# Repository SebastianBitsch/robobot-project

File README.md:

### Getting started

1. Connect to robot 
  ```bash
  ssh local@10.197.216.74
  ```

2. Login
  ```password: grenen```

3. Build
  ```bash
  cd svn/robobot/raubase/build && make
  ```

4. Run
  ```bash
  cd svn/robobot/raubase/build && ./raubase
  ```

### Tips and tricks
- Moving files from ```ssh``` to ```local```. On a terminal on your local machine: 
  ```bash
  scp -r local@10.197.216.74:/home/local/svn<PATH_TO_FILE> <LOCAL_PATH>
  ```
  - For instance:
  ```bash
  scp -r local@10.197.216.74:/home/local/svn/robobot/raubase/build/img/ /Users/sebastianbitsch/Desktop/
  ```

# Camera
Access the stream
```bash
cd svn/robobot/raubase/build/
motion
```
See the output stream at <http://10.197.216.74:8081>

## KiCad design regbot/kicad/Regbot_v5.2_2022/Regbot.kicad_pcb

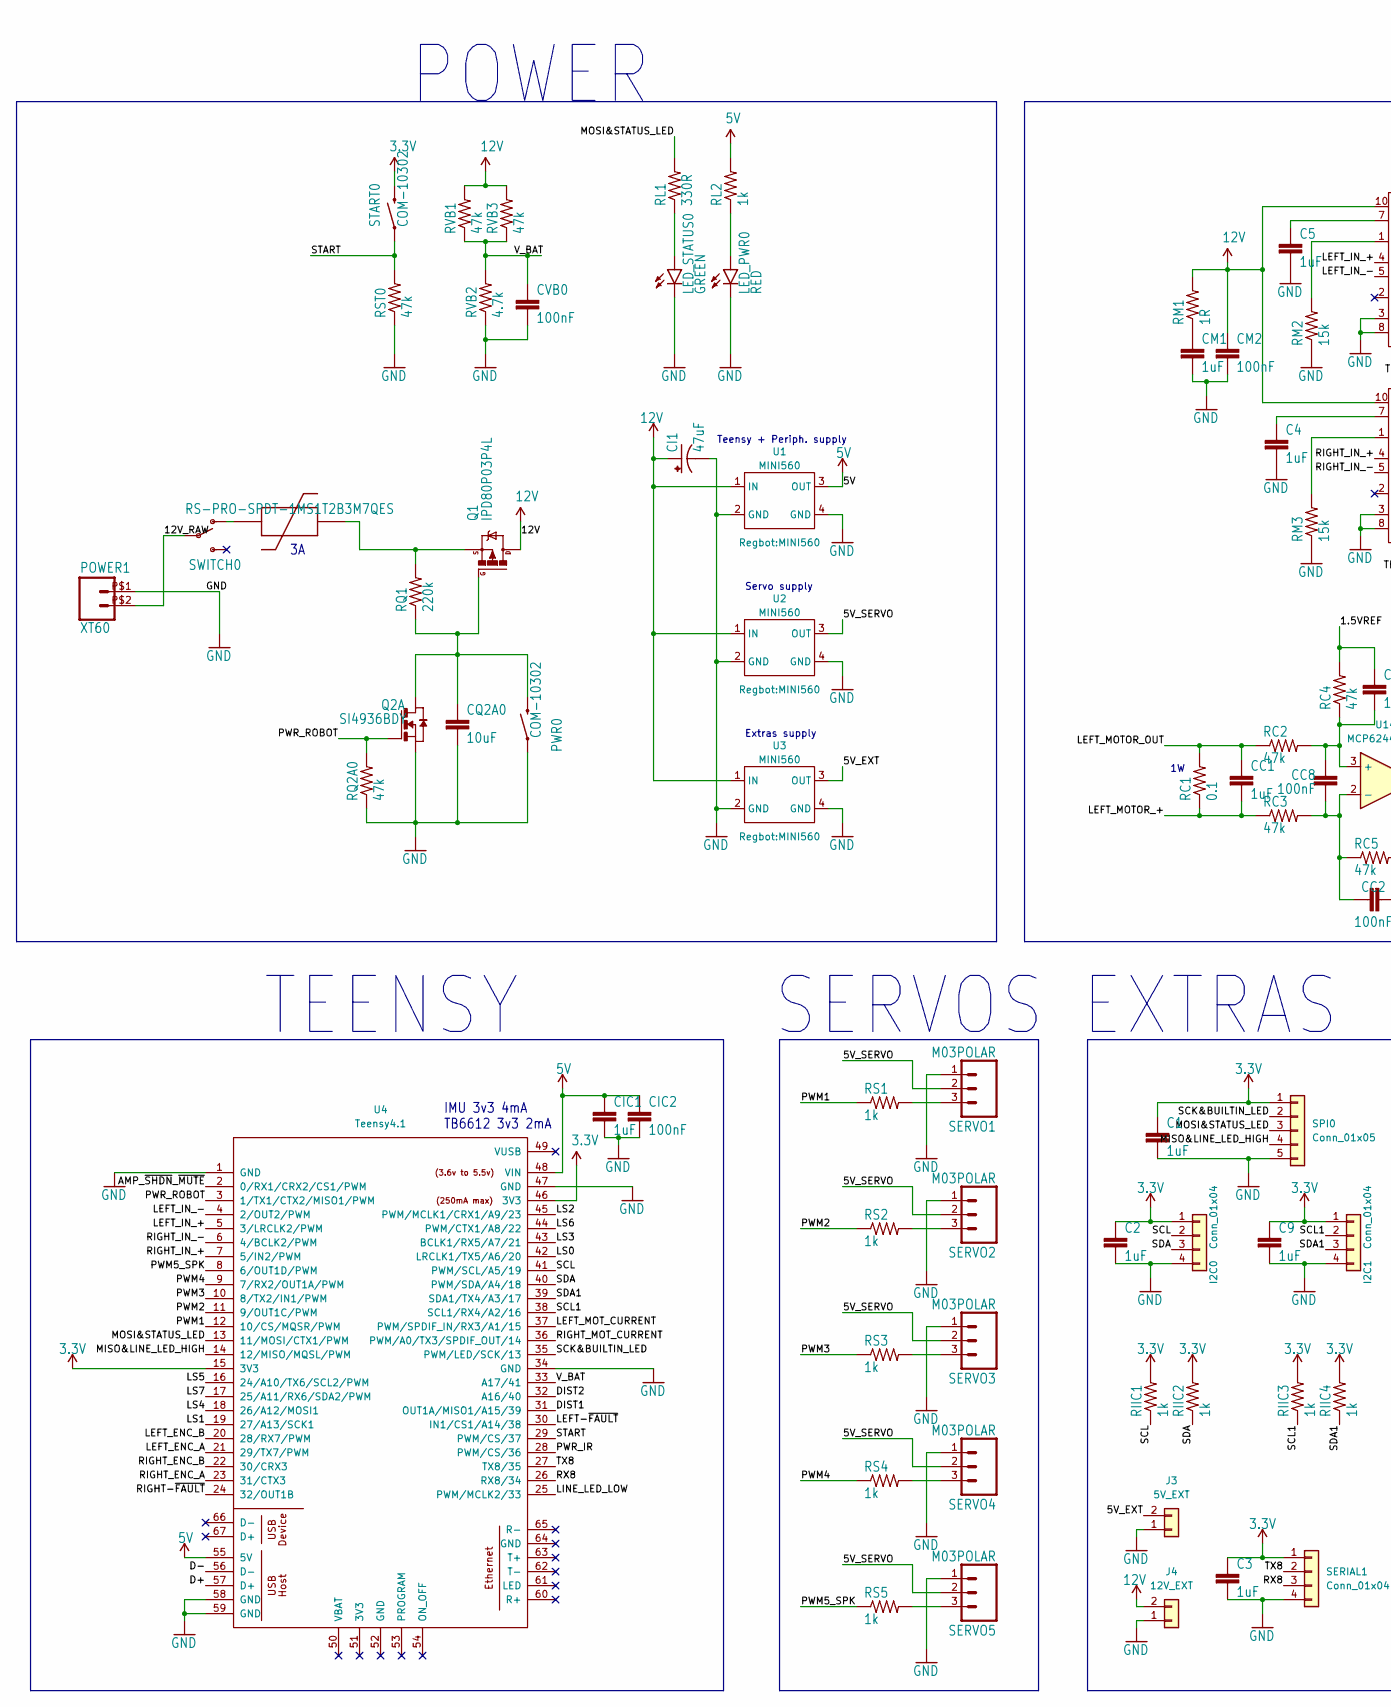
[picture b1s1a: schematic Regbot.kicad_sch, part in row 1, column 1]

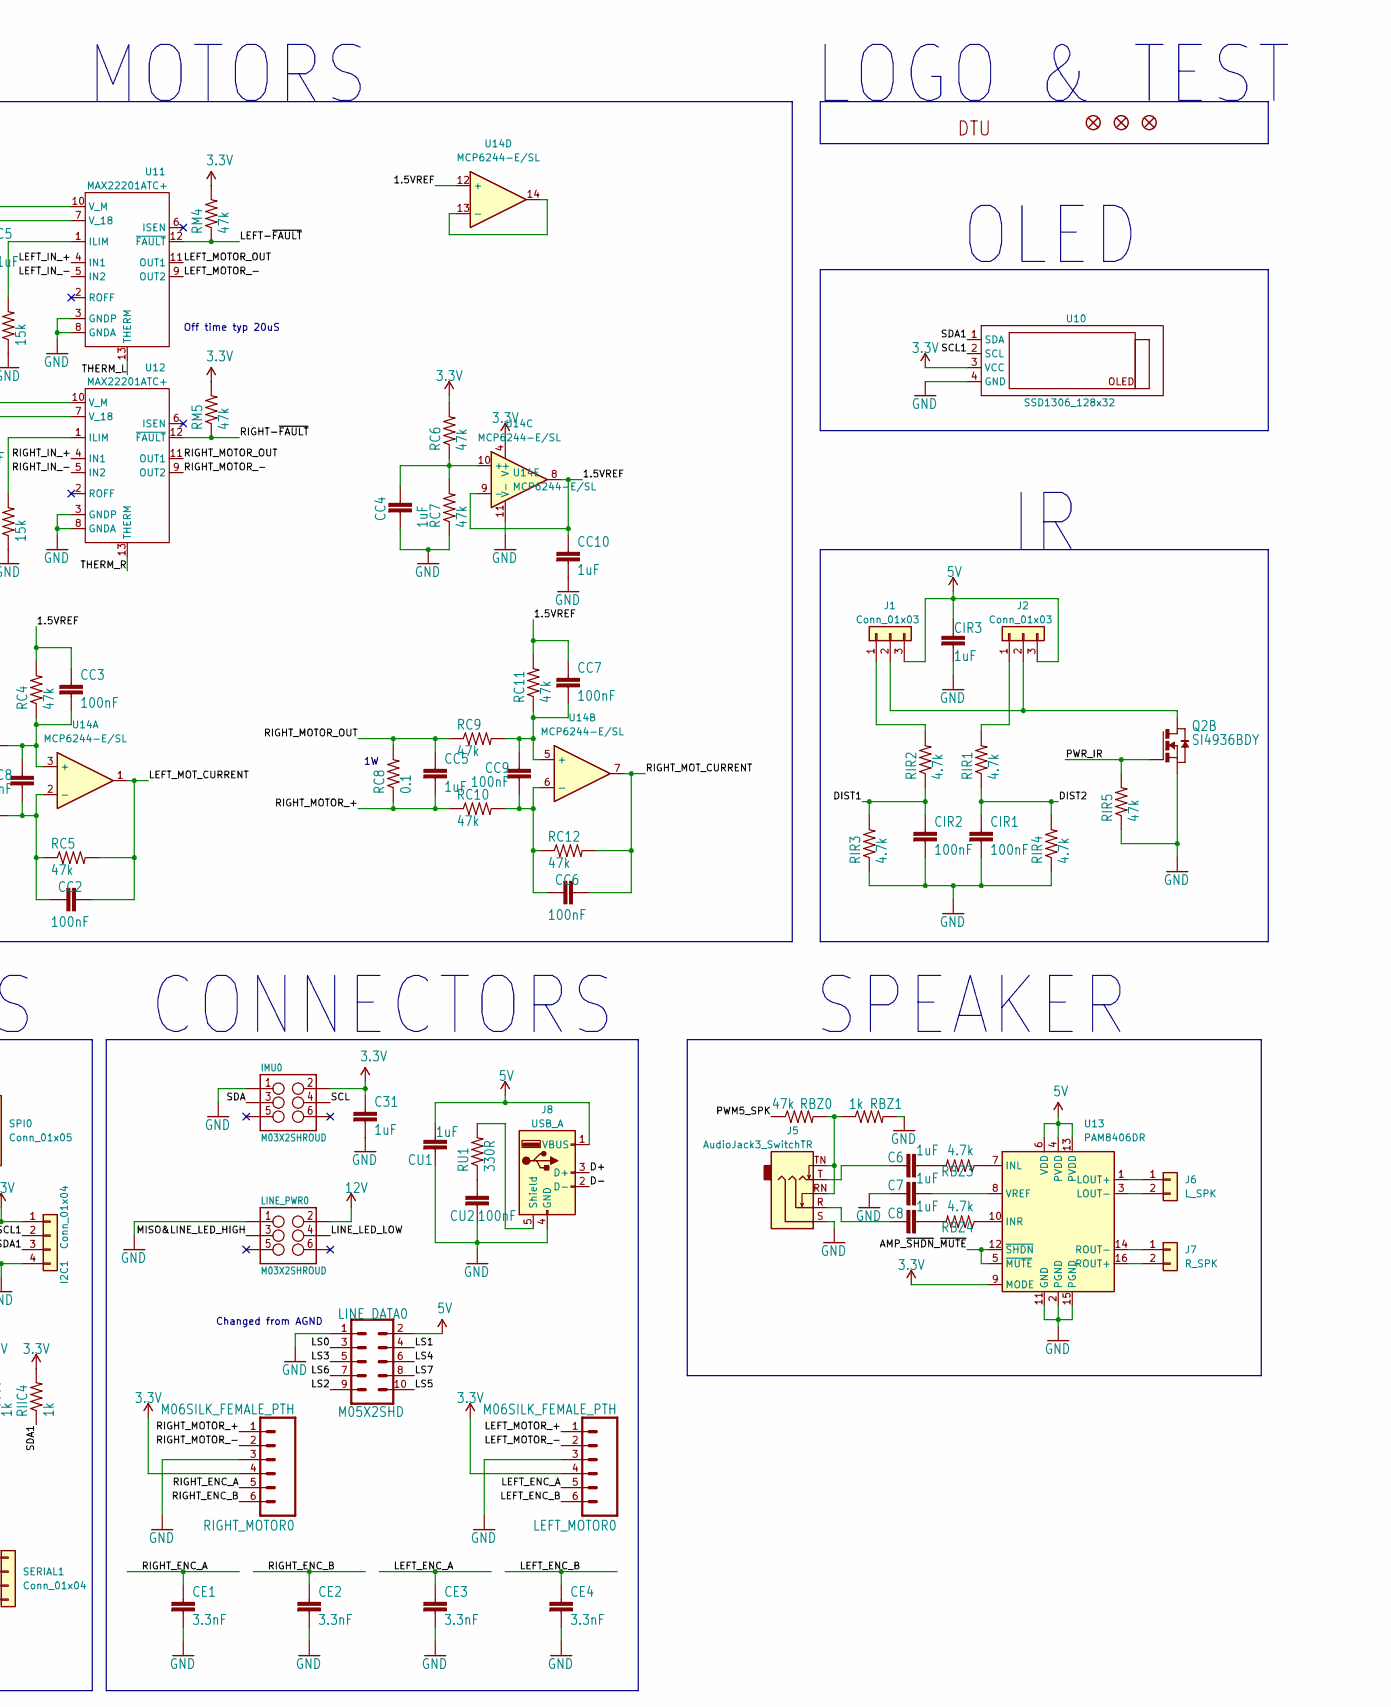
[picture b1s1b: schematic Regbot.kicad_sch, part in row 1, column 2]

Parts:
C1, C2, C3, C4, C5, C6, C7, C8, C9, C31: 1uF; 0805
CC1, CC4, CC5, CC10: 1uF; 0805
CC2, CC3, CC6, CC7, CC8, CC9: 100nF; 0805
CE1, CE2, CE3, CE4: 3.3nF; 0805
CI1: 47uF; PANASONIC_D_XL
CIC1: 1uF; 0805
CIC2: 100nF; 0805
CIR1, CIR2: 100nF; 0805
CIR3: 1uF; 0805
CM1: 1uF; 0805
CM2: 100nF; 0805
CQ2A0: 10uF; 1210
CU1: 1uF; 0805
CU2: 100nF; 0805
CVB0: 100nF; 0805
FD1, FD2, FD3: FIDUCIAL1X2; FIDUCIAL-1X2
I2C0, I2C1: Conn_01x04; JST_PH_B4B-PH-K_1x04_P2.00mm_Vertical
IMU0: 2X3-SHROUDED
J1, J2: Conn_01x03; JST_PH_B3B-PH-K_1x03_P2.00mm_Vertical
J3: 5V_EXT; JST_PH_B2B-PH-K_1x02_P2.00mm_Vertical
J4: 12V_EXT; JST_PH_B2B-PH-K_1x02_P2.00mm_Vertical
J5: AudioJack3_SwitchTR; STX-3680-5NB
J6: L_SPK; JST_PH_B2B-PH-K_1x02_P2.00mm_Vertical
J7: R_SPK; JST_PH_B2B-PH-K_1x02_P2.00mm_Vertical
J8: USB_A; USB_A_ASSMANN_A-TOP_VERTICAL
LED_PWR0: RED; LED-1206
LED_STATUS0: GREEN; LED-1206
LEFT_MOTOR0: M06SILK_FEMALE_PTH; 1X06
LINE_DATA0: 2X5-SHROUDED
LINE_PWR0: 2X3-SHROUDED
MAIN_FUSE0: SMF_OMNI-BLOK_FUSE_BLOCK
POWER1: XT60
PWR0: COM-10302; TACTILE-PTH-12MM
Q1: D-PAK_TO252AA
Q2: SI4936BDY; SO8
RBZ0: 47k; 0805
RBZ1: 1k; 0805
RBZ3, RBZ4: 4.7k; 0805
RC1, RC8: 0.1; R_1206_3216Metric
RC2, RC3, RC4, RC5, RC6, RC7, RC9, RC10, RC11, RC12: 47k; 0805
RIGHT_MOTOR0: M06SILK_FEMALE_PTH; 1X06
RIIC1, RIIC2, RIIC3, RIIC4: 1k; 0805
RIR1, RIR2, RIR3, RIR4: 4.7k; 0805
RIR5: 47k; 0805
RL1: 330R; 0805
RL2: 1k; 0805
RM1: 1R; 0805
RM2, RM3: 15k; 0805
RM4, RM5: 47k; 0805
RQ1: 220k; 0805
RQ2A0: 47k; 0805
RS1, RS2, RS3, RS4, RS5: 1k; 0805
RST0: 47k; 0805
RU1: 330R; 0805
RVB1, RVB3: 47k; 0805
RVB2: 4.7k; 0805
SERIAL1: Conn_01x04; JST_PH_B4B-PH-K_1x04_P2.00mm_Vertical
SERVO1, SERVO2, SERVO3, SERVO4, SERVO5: M03POLAR; MOLEX-1X3
SPI0: Conn_01x05; JST_PH_B5B-PH-K_1x05_P2.00mm_Vertical
START0: COM-10302; TACTILE-PTH-12MM
SWITCH0: RS-PRO-1MS1T2B3M7QES
U1, U2, U3: MINI560
U4: Teensy4.1; Teensy41
U10: SSD1306_128x32
U11, U12: MAX22201ATC+; SON50P300X300X80-13N
U13: PAM8406DR; SOP-16_3.9x9.9mm_P1.27mm
U14: MCP6244-E/SL; SOIC-14_3.9x8.7mm_P1.27mm
U$1: DTUMEDIUM-9MM; DTU-MEDIUM-9MM

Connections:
3.3V: C1.1, C2.1, C3.1, C9.1, C31.1, I2C0.1, I2C1.1, IMU0.2, LEFT_MOTOR0.4, RC6.2, RIGHT_MOTOR0.4, RIIC1.2, RIIC2.2, RIIC3.2, RIIC4.2, RM4.2, RM5.2, SERIAL1.1, SPI0.1, START0.3, START0.4, U4.15 (3V3), U4.46 (3V3), U10.3 (VCC), U13.9 (MODE), U14.4 (V+)
5V: CIC1.1, CIC2.1, CIR3.1, CU1.1, J1.3, J2.3, J8.1 (VBUS), LINE_DATA0.2, RL2.2, U1.3 (OUT), U4.48 (VIN), U4.55 (5V), U13.4 (PVDD), U13.6 (VDD), U13.13 (PVDD)
12V: CI1.+, CM2.1, J4.2, LINE_PWR0.2, Q1.4 (D), RM1.2, RVB1.2, RVB3.2, U1.1 (IN), U2.1 (IN), U3.1 (IN), U11.10 (V_M), U12.10 (V_M)
/1.5VREF: CC3.1, CC7.1, CC10.1, RC4.2, RC11.2, U14.8, U14.9 (-), U14.12 (+)
/5V_EXT: J3.2, U3.3 (OUT)
/5V_SERVO: SERVO1.2, SERVO2.2, SERVO3.2, SERVO4.2, SERVO5.2, U2.3 (OUT)
/12V_RAW: POWER1.P$2 (2), SWITCH0.P$2 (P2)
/AMP_~SHDN_~MUTE: U4.2 (0/RX1/CRX2/CS1/PWM), U13.5 (~MUTE), U13.12 (~SHDN)
/D+: J8.3 (D+), U4.57 (D+)
/D-: J8.2 (D-), U4.56 (D-)
/DIST1: CIR2.1, RIR2.1, RIR3.2, U4.31 (OUT1A/MISO1/A15/39)
/DIST2: CIR1.1, RIR1.1, RIR4.2, U4.32 (A16/40)
/LEFT-~FAULT: RM4.1, U4.30 (IN1/CS1/A14/38), U11.12 (~FAULT)
/LEFT_ENC_A: CE3.1, LEFT_MOTOR0.5, U4.21 (29/TX7/PWM)
/LEFT_ENC_B: CE4.1, LEFT_MOTOR0.6, U4.20 (28/RX7/PWM)
/LEFT_IN_+: U4.5 (3/LRCLK2/PWM), U11.4 (IN1)
/LEFT_IN_-: U4.4 (2/OUT2/PWM), U11.5 (IN2)
/LEFT_MOTOR_+: CC1.2, LEFT_MOTOR0.1, RC1.1, RC3.1
/LEFT_MOTOR_-: LEFT_MOTOR0.2, U11.9 (OUT2)
/LEFT_MOTOR_OUT: CC1.1, RC1.2, RC2.1, U11.11 (OUT1)
/LEFT_MOT_CURRENT: CC2.1, RC5.2, U4.37 (PWM/SPDIF_IN/RX3/A1/15), U14.1
/LINE_LED_LOW: LINE_PWR0.4, U4.25 (PWM/MCLK2/33)
/LS0: LINE_DATA0.3, U4.42 (LRCLK1/TX5/A6/20)
/LS1: LINE_DATA0.4, U4.19 (27/A13/SCK1)
/LS2: LINE_DATA0.9, U4.45 (PWM/MCLK1/CRX1/A9/23)
/LS3: LINE_DATA0.5, U4.43 (BCLK1/RX5/A7/21)
/LS4: LINE_DATA0.6, U4.18 (26/A12/MOSI1)
/LS5: LINE_DATA0.10, U4.16 (24/A10/TX6/SCL2/PWM)
/LS6: LINE_DATA0.7, U4.44 (PWM/CTX1/A8/22)
/LS7: LINE_DATA0.8, U4.17 (25/A11/RX6/SDA2/PWM)
/MISO&LINE_LED_HIGH: LINE_PWR0.3, SPI0.4, U4.14 (12/MISO/MQSL/PWM)
/MOSI&STATUS_LED: RL1.2, SPI0.3, U4.13 (11/MOSI/CTX1/PWM)
/PWM1: RS1.1, U4.12 (10/CS/MQSR/PWM)
/PWM2: RS2.1, U4.11 (9/OUT1C/PWM)
/PWM3: RS3.1, U4.10 (8/TX2/IN1/PWM)
/PWM4: RS4.1, U4.9 (7/RX2/OUT1A/PWM)
/PWM5_SPK: RBZ0.1, RS5.1, U4.8 (6/OUT1D/PWM)
/PWR_IR: Q2.4 (G), RIR5.2, U4.28 (PWM/CS/36)
/PWR_ROBOT: Q2.2 (G), RQ2A0.2, U4.3 (1/TX1/CTX2/MISO1/PWM)
/RIGHT-~FAULT: RM5.1, U4.24 (32/OUT1B), U12.12 (~FAULT)
/RIGHT_ENC_A: CE1.1, RIGHT_MOTOR0.5, U4.23 (31/CTX3)
/RIGHT_ENC_B: CE2.1, RIGHT_MOTOR0.6, U4.22 (30/CRX3)
/RIGHT_IN_+: U4.7 (5/IN2/PWM), U12.4 (IN1)
/RIGHT_IN_-: U4.6 (4/BCLK2/PWM), U12.5 (IN2)
/RIGHT_MOTOR_+: CC5.2, RC8.1, RC10.1, RIGHT_MOTOR0.1
/RIGHT_MOTOR_-: RIGHT_MOTOR0.2, U12.9 (OUT2)
/RIGHT_MOTOR_OUT: CC5.1, RC8.2, RC9.1, U12.11 (OUT1)
/RIGHT_MOT_CURRENT: CC6.1, RC12.2, U4.36 (PWM/A0/TX3/SPDIF_OUT/14), U14.7
/RX8: SERIAL1.3, U4.26 (RX8/34)
/SCK&BUILTIN_LED: SPI0.2, U4.35 (PWM/LED/SCK/13)
/SCL: I2C0.2, IMU0.4, RIIC1.1, U4.41 (PWM/SCL/A5/19)
/SCL1: I2C1.2, RIIC3.1, U4.38 (SCL1/RX4/A2/16), U10.2 (SCL)
/SDA: I2C0.3, IMU0.3, RIIC2.1, U4.40 (PWM/SDA/A4/18)
/SDA1: I2C1.3, RIIC4.1, U4.39 (SDA1/TX4/A3/17), U10.1 (SDA)
/START: RST0.2, START0.1, START0.2, U4.29 (PWM/CS/37)
/THERM_L: U11.13 (THERM)
/THERM_R: U12.13 (THERM)
/TX8: SERIAL1.2, U4.27 (TX8/35)
/V_BAT: CVB0.1, RVB1.1, RVB2.2, RVB3.1, U4.33 (A17/41)
GND: C1.2, C2.2, C3.2, C4.2, C5.2, C7.1, C9.2, C31.2, CC4.2, CC10.2, CE1.2, CE2.2, CE3.2, CE4.2, CI1.-, CIC1.2, CIC2.2, CIR1.2, CIR2.2, CIR3.2, CM1.2, CM2.2, CQ2A0.2, CU1.2, CU2.2, CVB0.2, I2C0.4, I2C1.4, IMU0.1, J3.1, J4.1, J5.S, J8.4 (GND), LED_PWR0.C, LED_STATUS0.C, LEFT_MOTOR0.3, LINE_DATA0.1, LINE_PWR0.1, POWER1.P$1 (1), PWR0.1, PWR0.2, Q2.1 (S), Q2.3 (S), RBZ1.2, RC7.1, RIGHT_MOTOR0.3, RIR3.1, RIR4.1, RIR5.1, RM2.1, RM3.1, RQ2A0.1, RST0.1, RVB2.1, SERIAL1.4, SERVO1.1, SERVO2.1, SERVO3.1, SERVO4.1, SERVO5.1, SPI0.5, U1.2 (GND), U1.4 (GND), U2.2 (GND), U2.4 (GND), U3.2 (GND), U3.4 (GND), U4.1 (GND), U4.34 (GND), U4.47 (GND), U4.58 (GND), U4.59 (GND), U10.4 (GND), U11.3 (GNDP), U11.8 (GNDA), U12.3 (GNDP), U12.8 (GNDA), U13.2 (PGND), U13.11 (GND), U13.15 (PGND), U14.11 (V-)
unnamed: C4.1, U12.7 (V_18)
unnamed: C5.1, U11.7 (V_18)
unnamed: C6.1, J5.T
unnamed: C6.2, RBZ3.2
unnamed: C7.2, U13.8 (VREF)
unnamed: C8.1, J5.R
unnamed: C8.2, RBZ4.2
unnamed: CC2.2, CC8.2, RC3.2, RC5.1, U14.2 (-)
unnamed: CC3.2, CC8.1, RC2.2, RC4.1, U14.3 (+)
unnamed: CC4.1, RC6.1, RC7.2, U14.10 (+)
unnamed: CC6.2, CC9.2, RC10.2, RC12.1, U14.6 (-)
unnamed: CC7.2, CC9.1, RC9.2, RC11.1, U14.5 (+)
unnamed: CM1.1, RM1.1
unnamed: CQ2A0.1, PWR0.3, PWR0.4, Q1.1 (G), Q2.7 (D), Q2.8 (D), RQ1.1
unnamed: CU2.1, RU1.1
unnamed: J1.1, RIR2.2
unnamed: J1.2, J2.2, Q2.5 (D), Q2.6 (D)
unnamed: J2.1, RIR1.2
unnamed: J5.RN, J5.TN, RBZ0.2, RBZ1.1
unnamed: J6.1, U13.1 (LOUT+)
unnamed: J6.2, U13.3 (LOUT-)
unnamed: J7.1, U13.14 (ROUT-)
unnamed: J7.2, U13.16 (ROUT+)
unnamed: J8.5 (Shield), RU1.2
unnamed: LED_PWR0.A, RL2.1
unnamed: LED_STATUS0.A, RL1.1
unnamed: MAIN_FUSE0.PIN1, Q1.3 (S), RQ1.2
unnamed: MAIN_FUSE0.PIN2, SWITCH0.P$1 (O1)
unnamed: RBZ3.1, U13.7 (INL)
unnamed: RBZ4.1, U13.10 (INR)
unnamed: RM2.2, U11.1 (ILIM)
unnamed: RM3.2, U12.1 (ILIM)
unnamed: RS1.2, SERVO1.3
unnamed: RS2.2, SERVO2.3
unnamed: RS3.2, SERVO3.3
unnamed: RS4.2, SERVO4.3
unnamed: RS5.2, SERVO5.3
unnamed: U14.13 (-), U14.14

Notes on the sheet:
Changed from AGND
IMU 3v3 4mA TB6612 3v3 2mA
SPEAKER
Off time typ 20uS
Teensy + Periph. supply
TEENSY
Servo supply
MOTORS
POWER
SERVOS
OLED
EXTRAS
LOGO & TEST
CONNECTORS
Extras supply

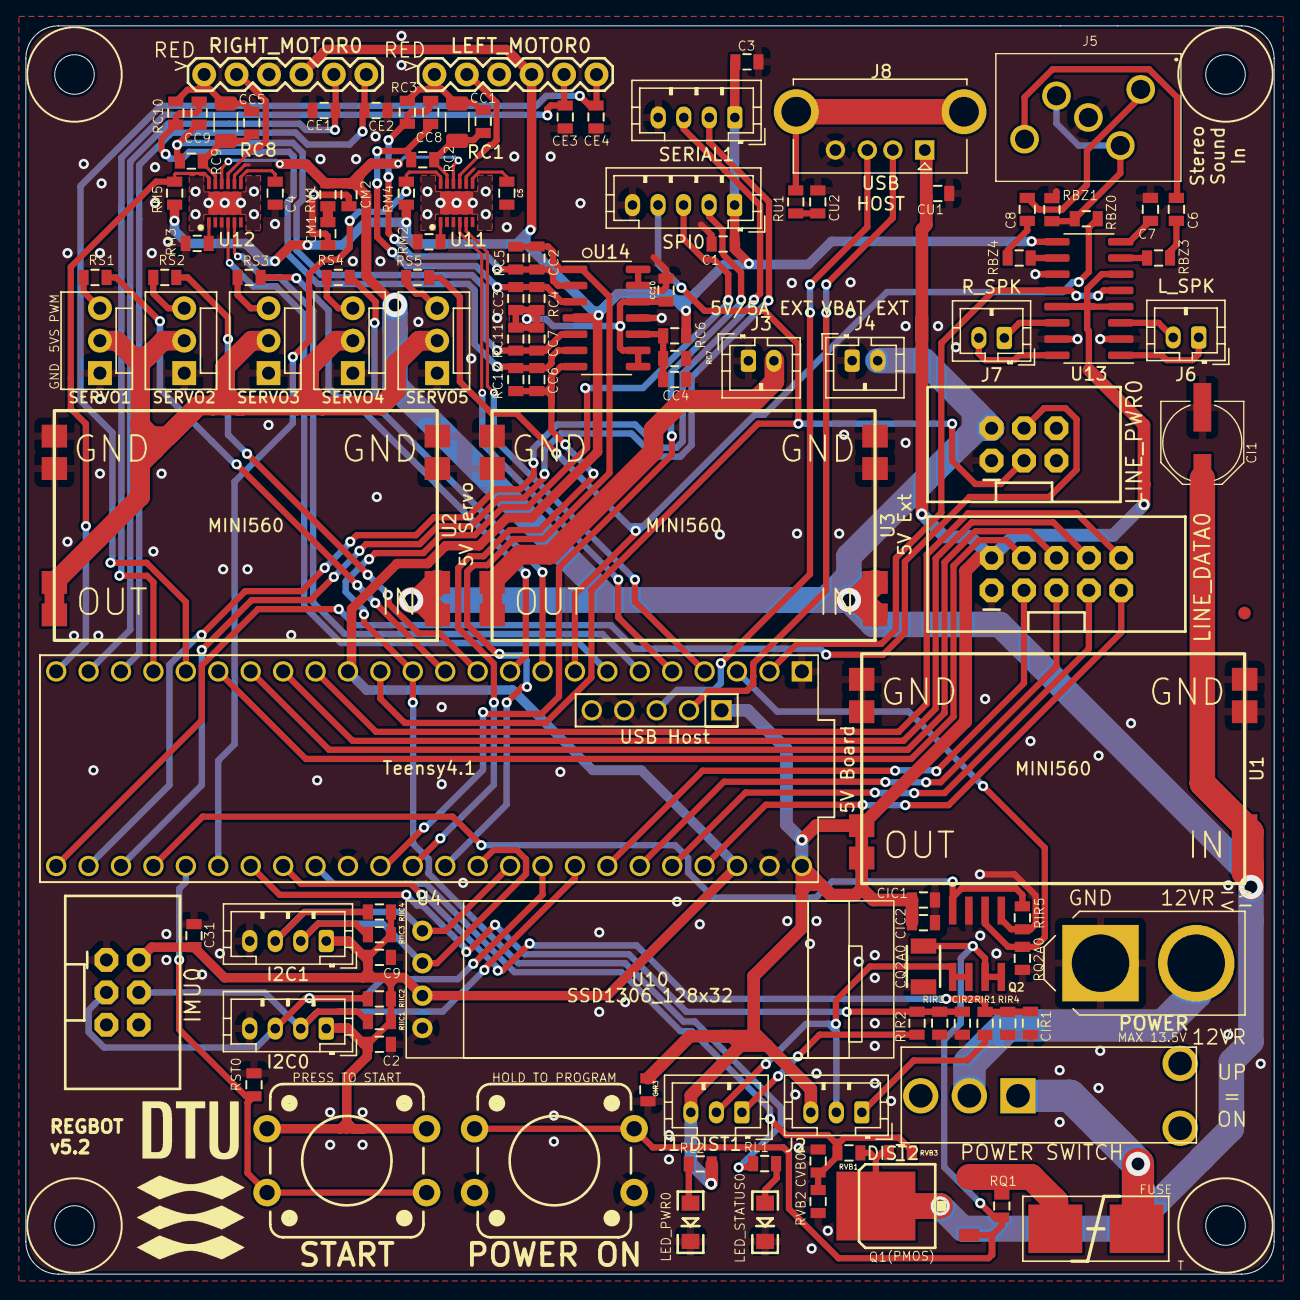
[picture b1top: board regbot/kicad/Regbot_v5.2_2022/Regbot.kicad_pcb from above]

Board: 2 copper layers, 97.8 x 97.8 mm, 129 parts (1 on the bottom side), 96 nets.

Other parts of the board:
@HOLE0, @HOLE1, @HOLE2, @HOLE3: (no value)
U$1#2: DTUMEDIUM-9MM; DTU-MEDIUM-9MM

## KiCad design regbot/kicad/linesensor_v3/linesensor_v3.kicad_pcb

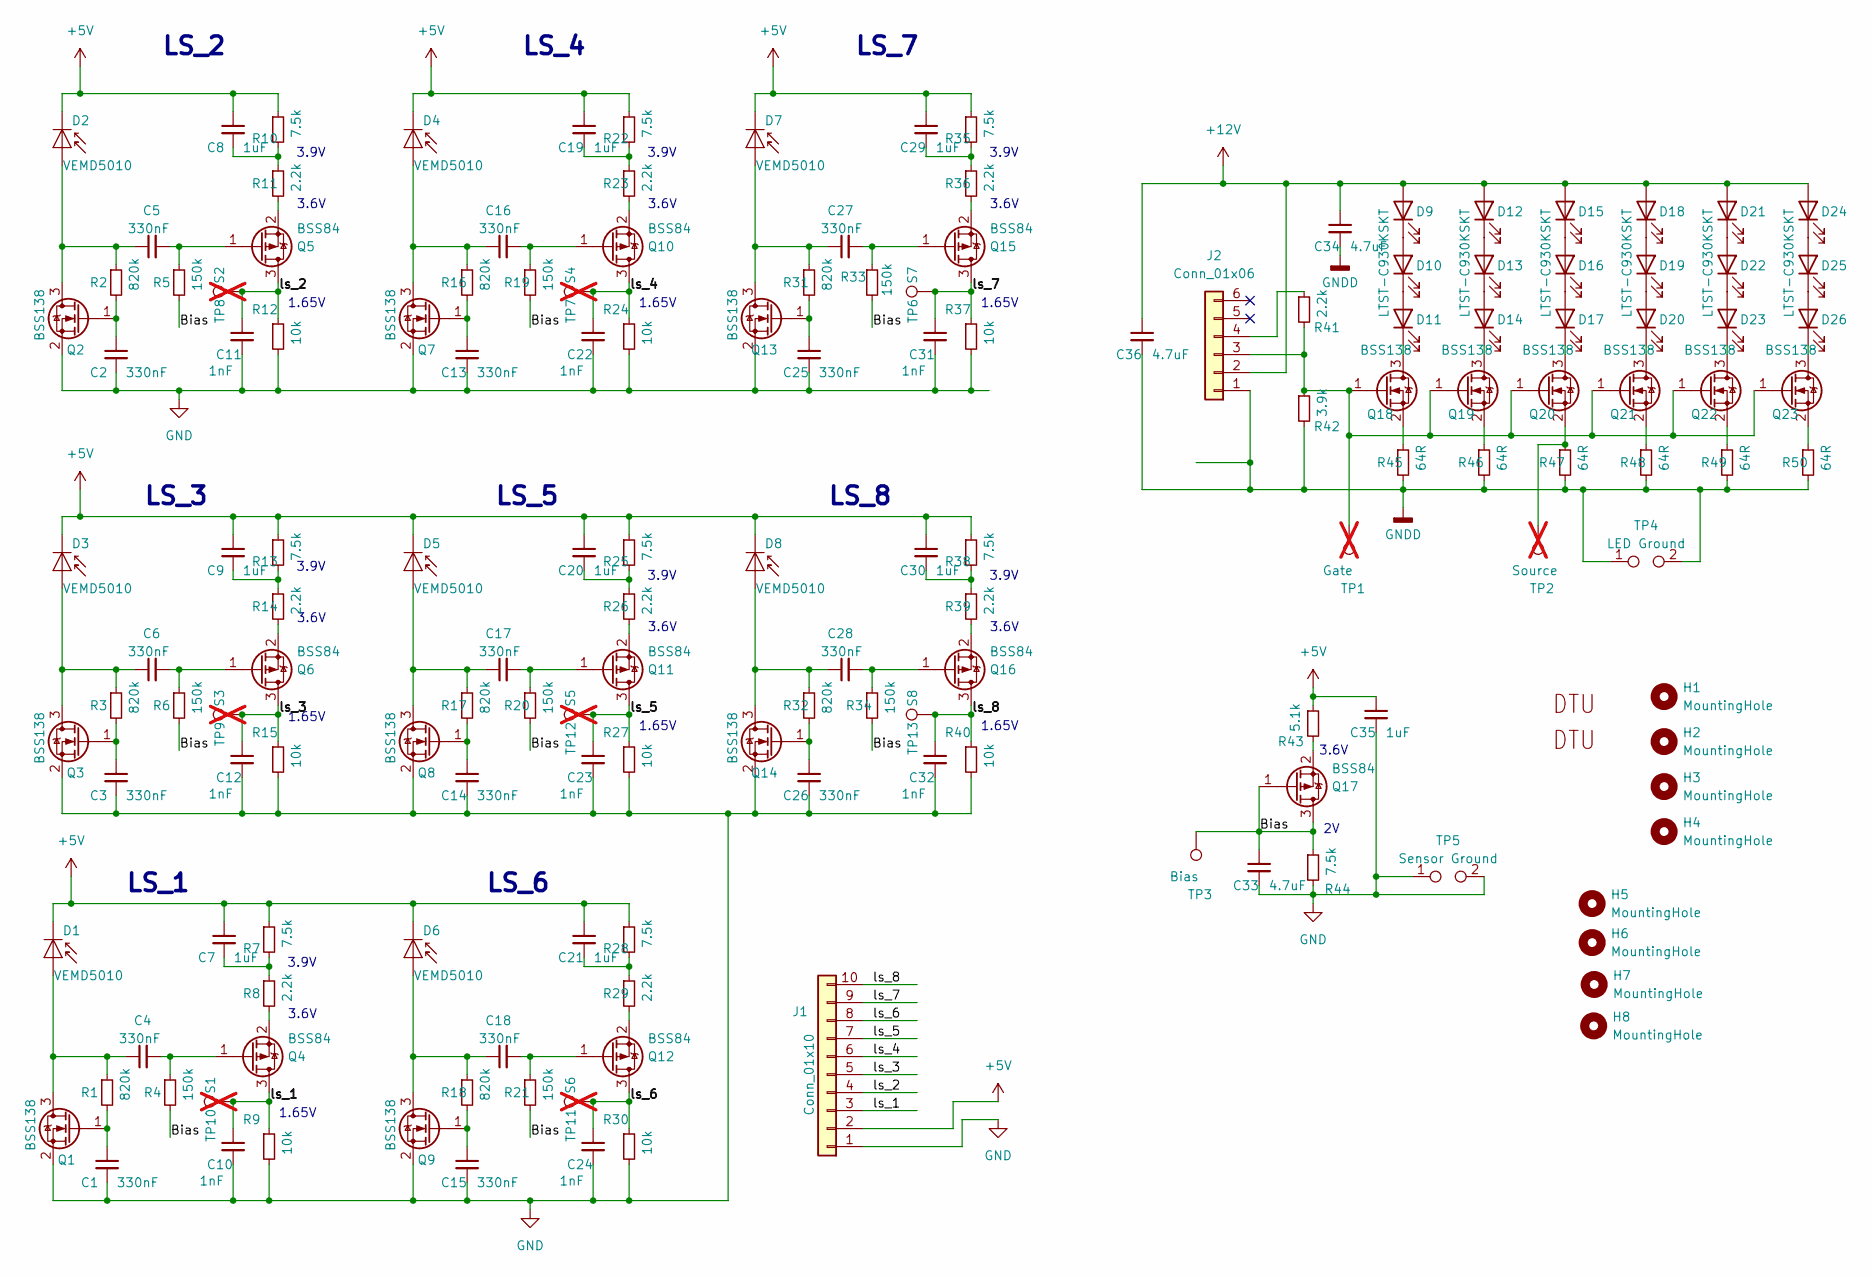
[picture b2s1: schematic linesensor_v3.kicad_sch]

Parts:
C1, C2, C3, C4, C5, C6, C13, C14, C15, C16, C17, C18, C25, C26, C27, C28: 330nF; C_0805_2012Metric
C7, C8, C9, C19, C20, C21, C29, C30, C35: 1uF; C_0805_2012Metric
C10, C11, C12, C22, C23, C24, C31, C32: 1nF; C_0805_2012Metric
C33, C34, C36: 4.7uF; C_0805_2012Metric
D1, D2, D3, D4, D5, D6, D7, D8: VEMD5010; SMT_VEMD5010
D9, D10, D11, D12, D13, D14, D15, D16, D17, D18, D19, D20, D21, D22, D23, D24, D25, D26: LTST-C930KSKT; LED_1210_3225Metric
H1, H2, H3, H4: MountingHole; MountingHole_3.2mm_M3
H5, H6, H7, H8: MountingHole; MountingHole_2.7mm_M2.5
J1: Conn_01x10; JST_PH_S10B-PH-SM4-TB_1x10-1MP_P2.00mm_Horizontal
J2: Conn_01x06; JST_PH_S6B-PH-SM4-TB_1x06-1MP_P2.00mm_Horizontal
L1: DTULARGE; DTU-LARGE
L2: DTUMEDIUM-13MM; DTU-MEDIUM-9MM
Q1, Q2, Q3, Q7, Q8, Q9, Q13, Q14, Q18, Q19, Q20, Q21, Q22, Q23: BSS138; SOT-23
Q4, Q5, Q6, Q10, Q11, Q12, Q15, Q16, Q17: BSS84; SOT-23
R1, R2, R3, R16, R17, R18, R31, R32: 820k; R_0805_2012Metric
R4, R5, R6, R19, R20, R21, R33, R34: 150k; R_0805_2012Metric
R7, R10, R13, R22, R25, R28, R35, R38, R44: 7.5k; R_0805_2012Metric
R8, R11, R14, R23, R26, R29, R36, R39, R41: 2.2k; R_0805_2012Metric
R9, R12, R15, R24, R27, R30, R37, R40: 10k; R_0805_2012Metric
R42: 3.9k; R_0805_2012Metric
R43: 5.1k; R_0805_2012Metric
R45, R46, R47, R48, R49, R50: 64R; R_0805_2012Metric
TP1: Gate; TestPoint_Pad_D2.0mm; not fitted
TP2: Source; TestPoint_Pad_D2.0mm; not fitted
TP3: Bias; TestPoint_Pad_D2.0mm
TP4: LED Ground; TestPoint_2Pads_Pitch2.54mm_Drill0.8mm
TP5: Sensor Ground; TestPoint_2Pads_Pitch2.54mm_Drill0.8mm
TP6: S7; TestPoint_Pad_D2.0mm
TP7: S4; TestPoint_Pad_D2.0mm; not fitted
TP8: S2; TestPoint_Pad_D2.0mm; not fitted
TP9: S3; TestPoint_Pad_D2.0mm; not fitted
TP10: S1; TestPoint_Pad_D2.0mm; not fitted
TP11: S6; TestPoint_Pad_D2.0mm; not fitted
TP12: S5; TestPoint_Pad_D2.0mm; not fitted
TP13: S8; TestPoint_Pad_D2.0mm

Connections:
+5V: C7.1, C8.1, C9.1, C19.1, C20.1, C21.1, C29.1, C30.1, C35.1, D1.1 (K), D2.1 (K), D3.1 (K), D4.1 (K), D5.1 (K), D6.1 (K), D7.1 (K), D8.1 (K), J1.2, R7.1, R10.1, R13.1, R22.1, R25.1, R28.1, R35.1, R38.1, R43.1
+12V: C34.1, C36.1, D9.2 (A), D12.2 (A), D15.2 (A), D18.2 (A), D21.2 (A), D24.2 (A), J2.2
/Bias: C33.1, Q17.1 (G), Q17.3 (D), R4.2, R5.2, R6.2, R19.2, R20.2, R21.2, R33.2, R34.2, R44.1, TP3.1
/ls_1: C10.1, J1.3, Q4.3 (D), R9.1, TP10.1
/ls_2: C11.1, J1.4, Q5.3 (D), R12.1, TP8.1
/ls_3: C12.1, J1.5, Q6.3 (D), R15.1, TP9.1
/ls_4: C22.1, J1.6, Q10.3 (D), R24.1, TP7.1
/ls_5: C23.1, J1.7, Q11.3 (D), R27.1, TP12.1
/ls_6: C24.1, J1.8, Q12.3 (D), R30.1, TP11.1
/ls_7: C31.1, J1.9, Q15.3 (D), R37.1, TP6.1
/ls_8: C32.1, J1.10, Q16.3 (D), R40.1, TP13.1
GND: C1.2, C2.2, C3.2, C10.2, C11.2, C12.2, C13.2, C14.2, C15.2, C22.2, C23.2, C24.2, C25.2, C26.2, C31.2, C32.2, C33.2, C35.2, J1.1, Q1.2 (S), Q2.2 (S), Q3.2 (S), Q7.2 (S), Q8.2 (S), Q9.2 (S), Q13.2 (S), Q14.2 (S), R9.2, R12.2, R15.2, R24.2, R27.2, R30.2, R37.2, R40.2, R44.2, TP5.1, TP5.2
GNDD: C34.2, C36.2, J2.1, R42.2, R45.2, R46.2, R47.2, R48.2, R49.2, R50.2, TP4.1, TP4.2
unnamed: C7.2, R7.2, R8.1
unnamed: C8.2, R10.2, R11.1
unnamed: C9.2, R13.2, R14.1
unnamed: C19.2, R22.2, R23.1
unnamed: C20.2, R25.2, R26.1
unnamed: C21.2, R28.2, R29.1
unnamed: C29.2, R35.2, R36.1
unnamed: C30.2, R38.2, R39.1
unnamed: C4.1, D1.2 (A), Q1.3 (D), R1.1
unnamed: C5.1, D2.2 (A), Q2.3 (D), R2.1
unnamed: C6.1, D3.2 (A), Q3.3 (D), R3.1
unnamed: C16.1, D4.2 (A), Q7.3 (D), R16.1
unnamed: C17.1, D5.2 (A), Q8.3 (D), R17.1
unnamed: C18.1, D6.2 (A), Q9.3 (D), R18.1
unnamed: C27.1, D7.2 (A), Q13.3 (D), R31.1
unnamed: C28.1, D8.2 (A), Q14.3 (D), R32.1
unnamed: D9.1 (K), D10.2 (A)
unnamed: D10.1 (K), D11.2 (A)
unnamed: D11.1 (K), Q18.3 (D)
unnamed: D12.1 (K), D13.2 (A)
unnamed: D13.1 (K), D14.2 (A)
unnamed: D14.1 (K), Q19.3 (D)
unnamed: D15.1 (K), D16.2 (A)
unnamed: D16.1 (K), D17.2 (A)
unnamed: D17.1 (K), Q20.3 (D)
unnamed: D18.1 (K), D19.2 (A)
unnamed: D19.1 (K), D20.2 (A)
unnamed: D20.1 (K), Q21.3 (D)
unnamed: D21.1 (K), D22.2 (A)
unnamed: D22.1 (K), D23.2 (A)
unnamed: D23.1 (K), Q22.3 (D)
unnamed: D24.1 (K), D25.2 (A)
unnamed: D25.1 (K), D26.2 (A)
unnamed: D26.1 (K), Q23.3 (D)
unnamed: J2.3, Q18.1 (G), Q19.1 (G), Q20.1 (G), Q21.1 (G), Q22.1 (G), Q23.1 (G), R41.2, R42.1, TP1.1
unnamed: J2.4, R41.1
unnamed: C1.1, Q1.1 (G), R1.2
unnamed: C2.1, Q2.1 (G), R2.2
unnamed: C3.1, Q3.1 (G), R3.2
unnamed: C4.2, Q4.1 (G), R4.1
unnamed: Q4.2 (S), R8.2
unnamed: C5.2, Q5.1 (G), R5.1
unnamed: Q5.2 (S), R11.2
unnamed: C6.2, Q6.1 (G), R6.1
unnamed: Q6.2 (S), R14.2
unnamed: C13.1, Q7.1 (G), R16.2
unnamed: C14.1, Q8.1 (G), R17.2
unnamed: C15.1, Q9.1 (G), R18.2
unnamed: C16.2, Q10.1 (G), R19.1
unnamed: Q10.2 (S), R23.2
unnamed: C17.2, Q11.1 (G), R20.1
unnamed: Q11.2 (S), R26.2
unnamed: C18.2, Q12.1 (G), R21.1
unnamed: Q12.2 (S), R29.2
unnamed: C25.1, Q13.1 (G), R31.2
unnamed: C26.1, Q14.1 (G), R32.2
unnamed: C27.2, Q15.1 (G), R33.1
unnamed: Q15.2 (S), R36.2
unnamed: C28.2, Q16.1 (G), R34.1
unnamed: Q16.2 (S), R39.2
unnamed: Q17.2 (S), R43.2
unnamed: Q18.2 (S), R45.1
unnamed: Q19.2 (S), R46.1
unnamed: Q20.2 (S), R47.1, TP2.1
unnamed: Q21.2 (S), R48.1
unnamed: Q22.2 (S), R49.1
unnamed: Q23.2 (S), R50.1

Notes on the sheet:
1.65V
3.9V
LS_1
LS_5
LS_2
3.6V
LS_4
LS_6
LS_7
LS_3
LS_8

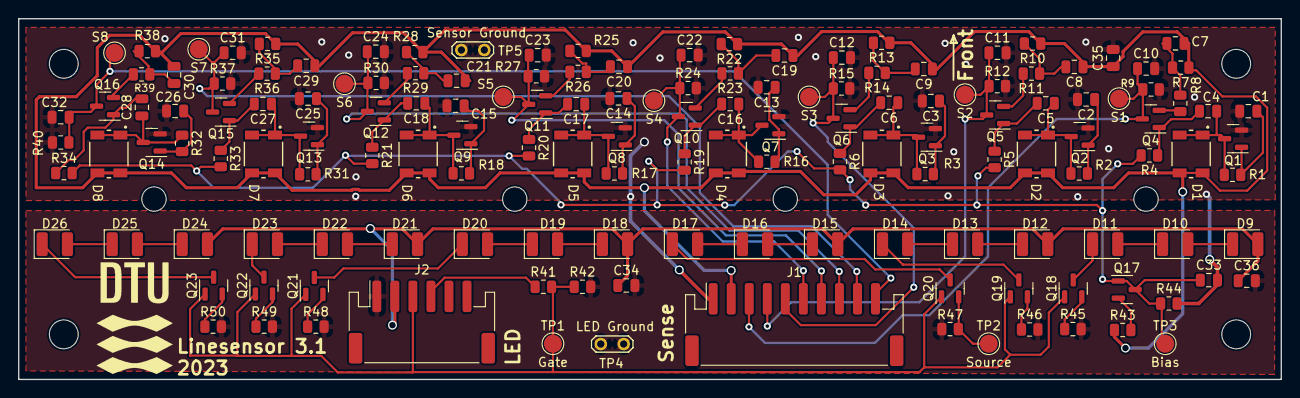
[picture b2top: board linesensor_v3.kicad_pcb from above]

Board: 2 copper layers, 140.0 x 40.0 mm, 160 parts (1 on the bottom side), 80 nets.
